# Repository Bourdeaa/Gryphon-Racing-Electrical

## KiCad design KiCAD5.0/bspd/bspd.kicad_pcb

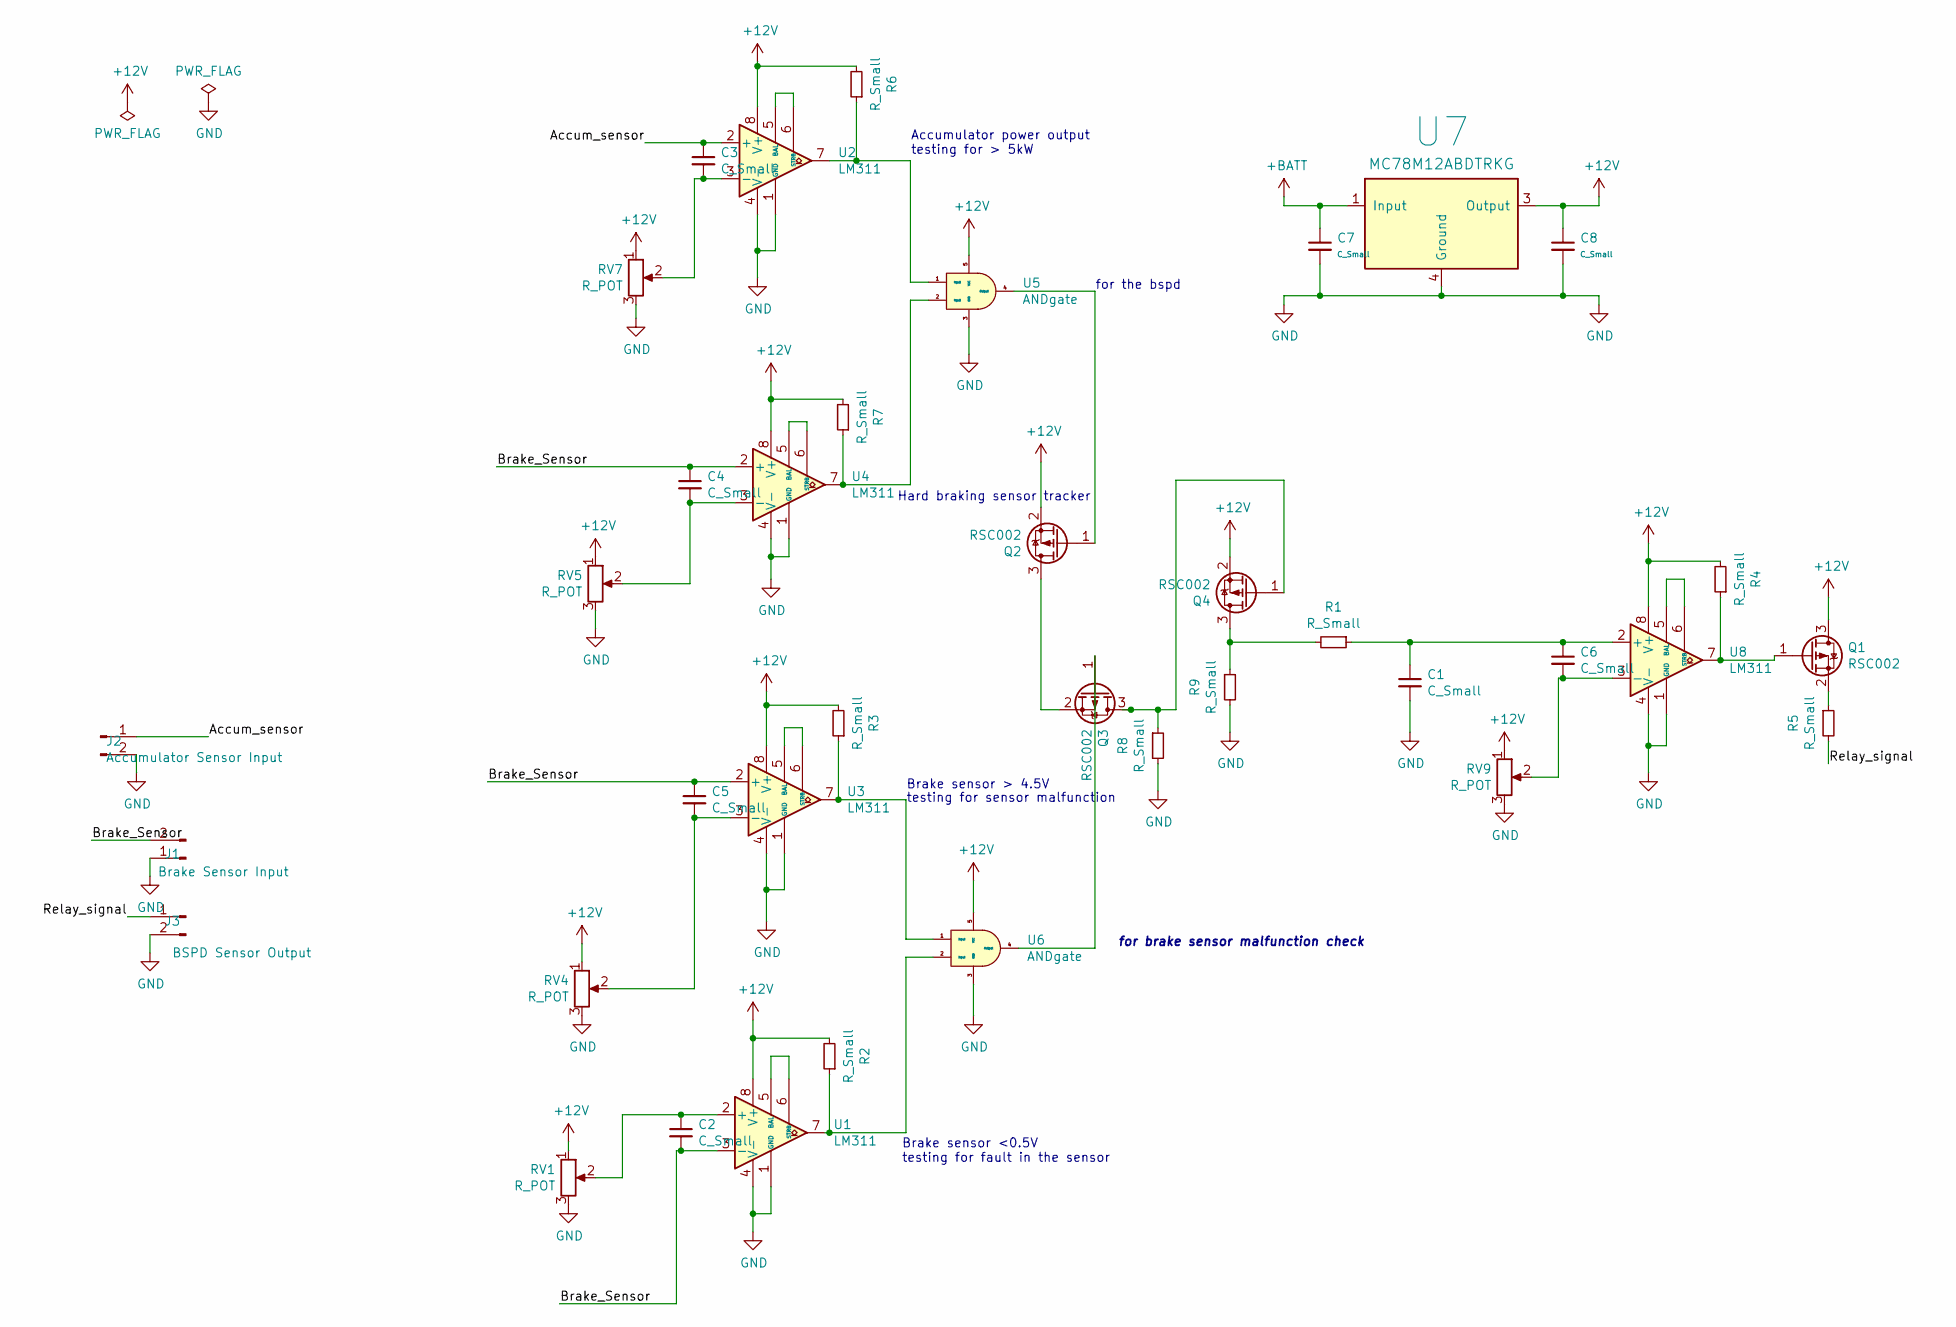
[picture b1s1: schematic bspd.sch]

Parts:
C1, C2, C3, C4, C5, C6, C7, C8: C_Small; C_1210_3225Metric_Pad1.33x2.70mm_HandSolder
J1: Brake Sensor Input; CUI_TBL001-500-02GY-2GY
J2: Accumulator Sensor Input; CUI_TBL001-500-02GY-2GY
J3: BSPD Sensor Output; CUI_TBL001-500-02GY-2GY
Q1, Q2, Q3, Q4: RSC002; BZT03C12-TR
R1, R2, R3, R4, R5, R6, R7, R8, R9: R_Small; R_0603_1608Metric_Pad0.98x0.95mm_HandSolder
RV1, RV4, RV5, RV7, RV9: R_POT; PT01-D120K2-B103
U1, U2, U3, U4, U8: LM311; LM311PW
U5, U6: ANDgate; SOT95P280X145-5N
U7: MC78M12ABDTRKG; TO229P990X238-4N

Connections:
+12V: C8.1, Q1.3 (D), Q2.2 (S), Q4.2 (S), R2.2, R3.2, R4.2, R6.2, R7.2, RV1.1, RV4.1, RV5.1, RV7.1, RV9.1, U1.8 (V+), U2.8 (V+), U3.8 (V+), U4.8 (V+), U5.5 (VCC), U6.5 (VCC), U7.3 (Output), U8.8 (V+)
+BATT: C7.1, U7.1 (Input)
/Accum_sensor: C3.1, J2.1, U2.2 (+)
/Brake_Sensor: C2.2, C4.1, C5.1, J1.2, U1.3 (-), U3.2 (+), U4.2 (+)
/Relay_signal: J3.1, R5.2
GND: C1.2, C7.2, C8.2, J1.1, J2.2, J3.2, R8.2, R9.2, RV1.3, RV4.3, RV5.3, RV7.3, RV9.3, U1.1 (GND), U1.4 (V-), U2.1 (GND), U2.4 (V-), U3.1 (GND), U3.4 (V-), U4.1 (GND), U4.4 (V-), U5.3 (GND), U6.3 (GND), U7.4 (Ground), U8.1 (GND), U8.4 (V-)
unnamed: C1.1, C6.1, R1.1, U8.2 (+)
unnamed: C2.1, RV1.2, U1.2 (+)
unnamed: C3.2, RV7.2, U2.3 (-)
unnamed: C4.2, RV5.2, U4.3 (-)
unnamed: C5.2, RV4.2, U3.3 (-)
unnamed: C6.2, RV9.2, U8.3 (-)
unnamed: Q1.1 (G), R4.1, U8.7
unnamed: Q1.2 (S), R5.1
unnamed: Q2.1 (G), U5.4 (Output)
unnamed: Q2.3 (D), Q3.2 (S)
unnamed: Q3.1 (G), U6.4 (Output)
unnamed: Q3.3 (D), Q4.1 (G), R8.1
unnamed: Q4.3 (D), R1.2, R9.1
unnamed: R2.1, U1.7, U6.2 (Input)
unnamed: R3.1, U3.7, U6.1 (Input)
unnamed: R6.1, U2.7, U5.1 (Input)
unnamed: R7.1, U4.7, U5.2 (Input)
unnamed: U1.5 (BAL), U1.6 (STRB)
unnamed: U2.5 (BAL), U2.6 (STRB)
unnamed: U3.5 (BAL), U3.6 (STRB)
unnamed: U4.5 (BAL), U4.6 (STRB)
unnamed: U8.5 (BAL), U8.6 (STRB)

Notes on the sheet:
for the bspd
for brake sensor malfunction check
Brake sensor <0.5V testing for fault in the sensor
Brake sensor > 4.5V
testing for sensor malfunction
Hard braking sensor tracker
Accumulator power output testing for > 5kW

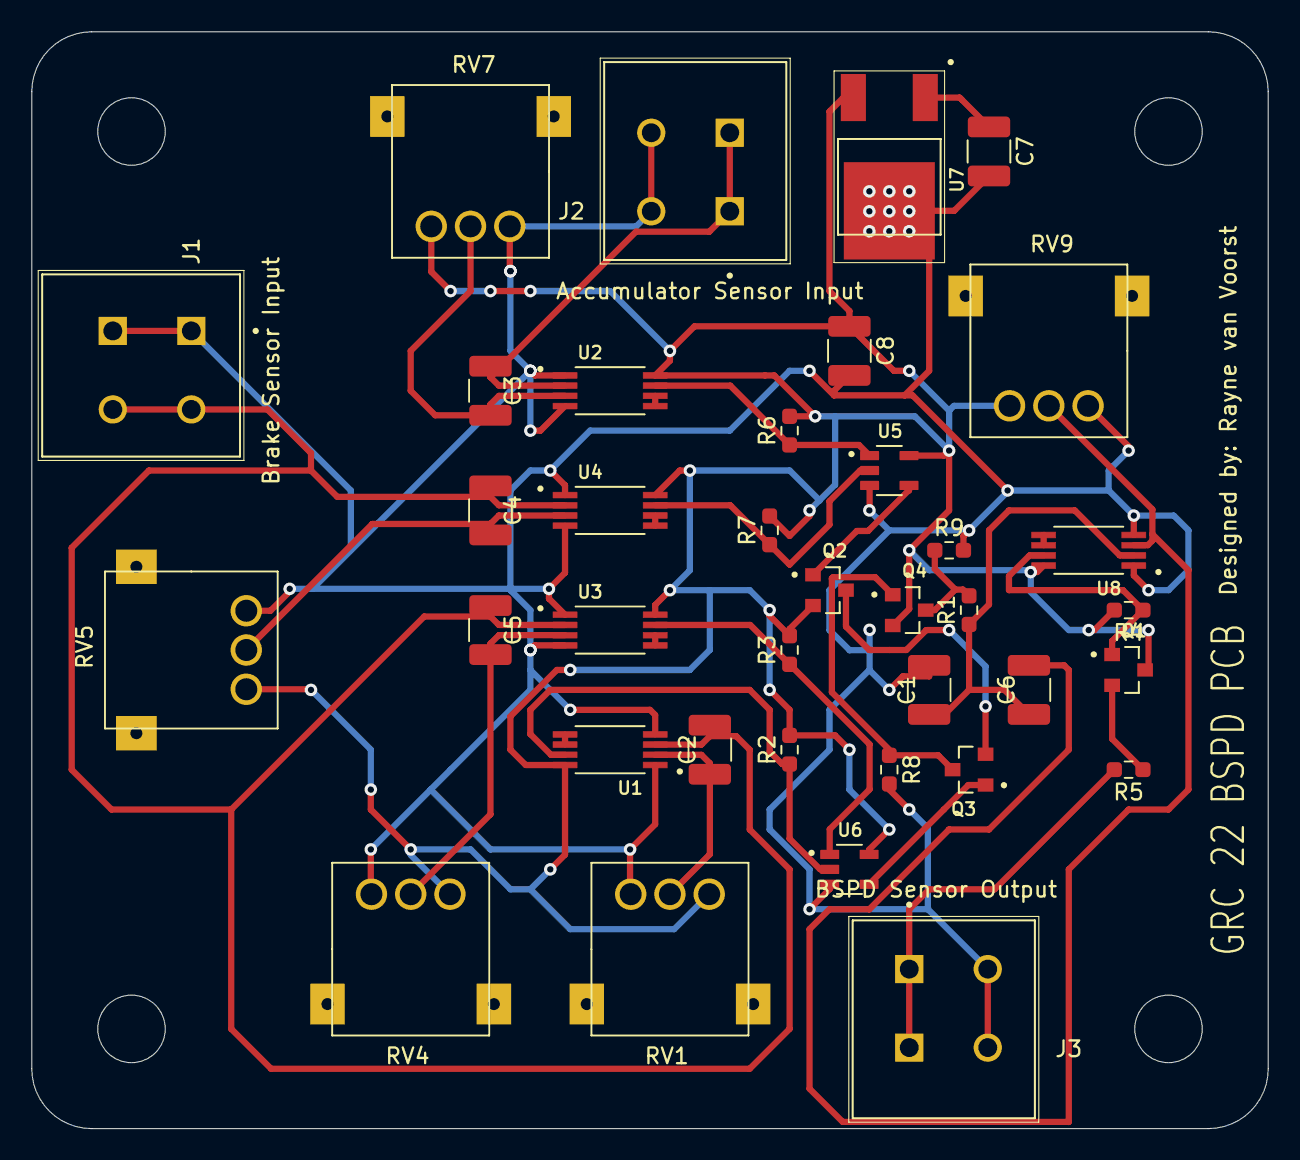
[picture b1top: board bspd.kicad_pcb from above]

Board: 2 copper layers, 78.7 x 69.9 mm, 37 parts (0 on the bottom side), 28 nets.

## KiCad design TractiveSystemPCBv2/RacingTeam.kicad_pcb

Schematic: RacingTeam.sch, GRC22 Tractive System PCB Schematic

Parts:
C1, C2: 470nF; C_0603_1608Metric_Pad1.08x0.95mm_HandSolder
C3, C4: 22μF; CAPE830X690N
C5, C6: 10nF; C_0603_1608Metric_Pad1.08x0.95mm_HandSolder
C7, C8: 100nF; C_0603_1608Metric_Pad1.08x0.95mm_HandSolder
C9, C10, C11, C12: 1μF; C_0603_1608Metric_Pad1.08x0.95mm_HandSolder
D1, D2: 12V; SOD57-10
D3, D8: LED; D_0805_2012Metric_Castellated
D4, D5, D6: Flyback; D_0805_2012Metric_Castellated
D7: D; D_0805_2012Metric_Castellated
F1, F2: Fuse_Small; FUSE_0154004.DRTL
J1: BusIn; TE_8PCV-02-006
J2: PowerInput; CUI_TBL001-500-02GY-2GY
J3: BrakePositionSensor; CUI_TBL001-500-02GY-2GY
J4: StartButton; CUI_TBL001-500-02GY-2GY
J5: Molex; 878310819
J6, J8, J10: BypassPin; PinHeader_1x01_P2.54mm_Vertical
J7: TSW-101-23-S-S; PinHeader_1x01_P2.54mm_Vertical
J9: PC Out; CUI_TBL001-500-02GY-2GY
J11: AIR Out; CUI_TBL001-500-02GY-2GY
J12: DischargeRelay; CUI_TBL001-500-02GY-2GY
JP1, JP2: Jumper; PinHeader_1x02_P2.54mm_Vertical
PS1: SPBW06F-12; CONV_SPBW06F-12; PARTREV N/A
Q1, Q2, Q3, Q7: 2N7002; 2N7002H6327XTSA2
Q4, Q5, Q6, Q8, Q9: RSC002; BZT03C12-TR
Q10: FMMT494QTA; SOT91P240X110-3N
Q11: RSC; BZT03C12-TR
R1, R2: 200kΩ; R_0805_2012Metric_Pad1.20x1.40mm_HandSolder
R3, R8: 25kΩ; R_0805_2012Metric_Pad1.20x1.40mm_HandSolder
R4, R5: 500kΩ; R_0805_2012Metric_Pad1.20x1.40mm_HandSolder
R6, R7: 150kΩ; R_0805_2012Metric_Pad1.20x1.40mm_HandSolder
R9, R10: 1kΩ; R_0603_1608Metric_Pad0.98x0.95mm_HandSolder
R11, R12: 0Ω; R_0603_1608Metric_Pad0.98x0.95mm_HandSolder
R14, R15, R16, R17: 100Ω; R_0603_1608Metric_Pad0.98x0.95mm_HandSolder
R18, R19: 20kΩ; R_0603_1608Metric_Pad0.98x0.95mm_HandSolder
R20, R21: 1.2kΩ; R_0603_1608Metric_Pad0.98x0.95mm_HandSolder
R22, R23, R28, R29: 10kΩ; R_0603_1608Metric_Pad0.98x0.95mm_HandSolder
R24, R26: 22kΩ; R_0603_1608Metric_Pad0.98x0.95mm_HandSolder
R25, R32: 499Ω; R_0603_1608Metric_Pad0.98x0.95mm_HandSolder
R27: 220kΩ; R_0603_1608Metric_Pad0.98x0.95mm_HandSolder
R30: 47kΩ; R_0603_1608Metric_Pad0.98x0.95mm_HandSolder
R31: 4.7kΩ; R_0603_1608Metric_Pad0.98x0.95mm_HandSolder
RV1, RV2: 10kΩ; PT01-D120K2-B103
U1, U2: LM2941LD; DFN400X400X80-9N
U3, U4: LM311; LM311PW
U5, U6: 4N35; OPTO_4N35SM
U7: NE555D; NE555PSRE4
U8: MC78M12ABDTRKG; TO229P990X238-4N

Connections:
+12V: C1.1, C2.1, PS1.6 (+VOUT), R18.2, R19.2, U1.3, U2.3, U3.8 (V+), U4.8 (V+), U5.1, U6.1
+BATT: C10.1, J2.2, PS1.2 (+VIN), U8.1 (Input)
/555Discharge: R26.2, R27.1, U7.7 (DIS)
/555DriveRED: Q7.3 (D), Q9.1 (G), R29.2
/555Output: Q7.1 (G), U7.3 (Q)
/555Reset: Q1.3 (D), Q4.1 (G), R24.2, U7.4 (R)
/555Trigger: C9.1, R27.2, U7.2 (TR), U7.6 (THR)
/AIR+: D6.1 (K), J11.1, Q2.1 (G), Q6.3 (D)
/BusLine: J1.1, R2.1
/BusOutPrecharge: F2.1, R3.1, R8.2, R12.2
/BusOutTSAL: F1.2, R6.2, R7.1, R11.2
/BusRefTSAL: D1.1 (K), F1.1, J8.1, R11.1, R14.2
/BusReturn: J1.2, R3.2
/Common: J3.2, J4.1
/Discharge: D5.1 (K), J12.1, Q2.2 (S), Q5.3 (D)
/Green+: J5.2, JP1.2, Q4.3 (D)
/InvertBus: Q1.1 (G), R23.1, U6.4
/OBLEDGreen: D3.2 (A), JP1.1
/OBLEDRed: D8.2 (A), JP2.2
/OBLEDResistorGreen: D3.1 (K), R25.1
/OBLEDResistorRed: D8.1 (K), R32.1
/PreChargeV+: C5.1, R17.1, U3.2 (+)
/Precharge-: D4.2 (A), J9.2, Q3.3 (D), Q5.1 (G)
/PrechargeCompOUT: R19.1, R20.1, U3.7
/PrechargeOPTO: Q3.1 (G), Q6.1 (G), Q11.1 (G), R22.2, U5.4
/PrechargeRef: C4.1, J7.1, R16.2, RV2.1, U2.5
/PrechargeV-: C5.2, R16.1, U3.3 (-)
/RED+: J5.3, JP2.1, Q9.3 (D)
/RTDLatch: J3.1, Q8.1 (G), Q10.2 (C), R28.1
/RTDOutput: C12.1, Q8.3 (D), Q11.2 (S)
/RTDReady: J5.4, Q11.3 (D)
/TSALCompOut: R18.1, R21.1, U4.7
/TSALRef: C3.1, J6.1, R15.2, RV1.1, U1.5
/TSAL_LM311V+: C6.1, R14.1, U4.2 (+)
/TSAL_LM311V-: C6.2, R15.1, U4.3 (-)
GLV+: C7.1, C11.1, D4.1 (K), J5.1, J9.1, Q2.3 (D), Q4.2 (S), Q5.2 (S), Q6.2 (S), Q8.2 (S), Q9.2 (S), R24.1, R26.1, R28.2, R29.1, U5.5, U6.5, U7.8 (VCC), U8.3 (Output)
GLV-: C7.2, C8.2, C9.2, C10.2, C11.2, D5.2 (A), D6.2 (A), D7.2 (A), J2.1, J4.2, J5.5, J5.6, J5.7, J5.8, J11.2, J12.2, PS1.1 (-VIN), Q1.2 (S), Q3.2 (S), Q7.2 (S), Q10.3 (E), R22.1, R23.2, R25.2, R30.2, R32.2, U7.1 (GND), U8.4 (Ground)
GND: C1.2, C2.2, C3.2, C4.2, D1.2 (A), D2.2 (A), PS1.7 (-VOUT), R9.1, R10.1, U1.1, U1.2, U1.7, U1.9, U2.1, U2.2, U2.7, U2.9, U3.1 (GND), U3.4 (V-), U4.1 (GND), U4.4 (V-)
unnamed: C8.1, U7.5 (CV)
unnamed: C12.2, D7.1 (K), R31.2
unnamed: D2.1 (K), F2.2, J10.1, R12.1, R17.2
unnamed: Q10.1 (B), R30.1, R31.1
unnamed: R1.1, R2.2
unnamed: R1.2, R4.2
unnamed: R4.1, R5.2
unnamed: R5.1, R6.1
unnamed: R7.2, R8.1
unnamed: R9.2, RV1.2, U1.8
unnamed: R10.2, RV2.2, U2.8
unnamed: R20.2, U5.2
unnamed: R21.2, U6.2
unnamed: U3.5 (BAL), U3.6 (STRB)
unnamed: U4.5 (BAL), U4.6 (STRB)

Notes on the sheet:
TSAL
Isolation Barrier
TSAL Trigger Voltage = 60V Voltage Division Ratio = 0.8857 60V- 60(0.8857) = 6.86V
Comparator Logic If V- > V+ || Output is pulled to GND If V+ > V- || Inner Transistor is not conducting
12V+ - High Voltage Regulated 12V (From HV Regulator) GND - High Voltage Regulated Isolated Ground (From HV Regulator) +BATT - Unregulated Battery Supply + -BATT - Unregulated Battery Supply - (Synced to GLV-) GLV+ - Grounded Low Voltage + (from GLV Regulator) GLV- - Grounded Low Voltage - (From GL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
If=10mA
GLV
BoardOutputs
Discharge Control
Power Symbol Definitions
GLV Regulator
Source Gate Drain
Ready To Drive
PCR
AIR
BoardInputs
PreCharge Control
RelayOutputs
Latch Activation
Precharge Trigger Voltage = 525V Voltage Division Ratio = 0.9857 525V- 525(0.9857) = 7.5V
Trim Pot to 5.9k
Trim Pot to 5.4k

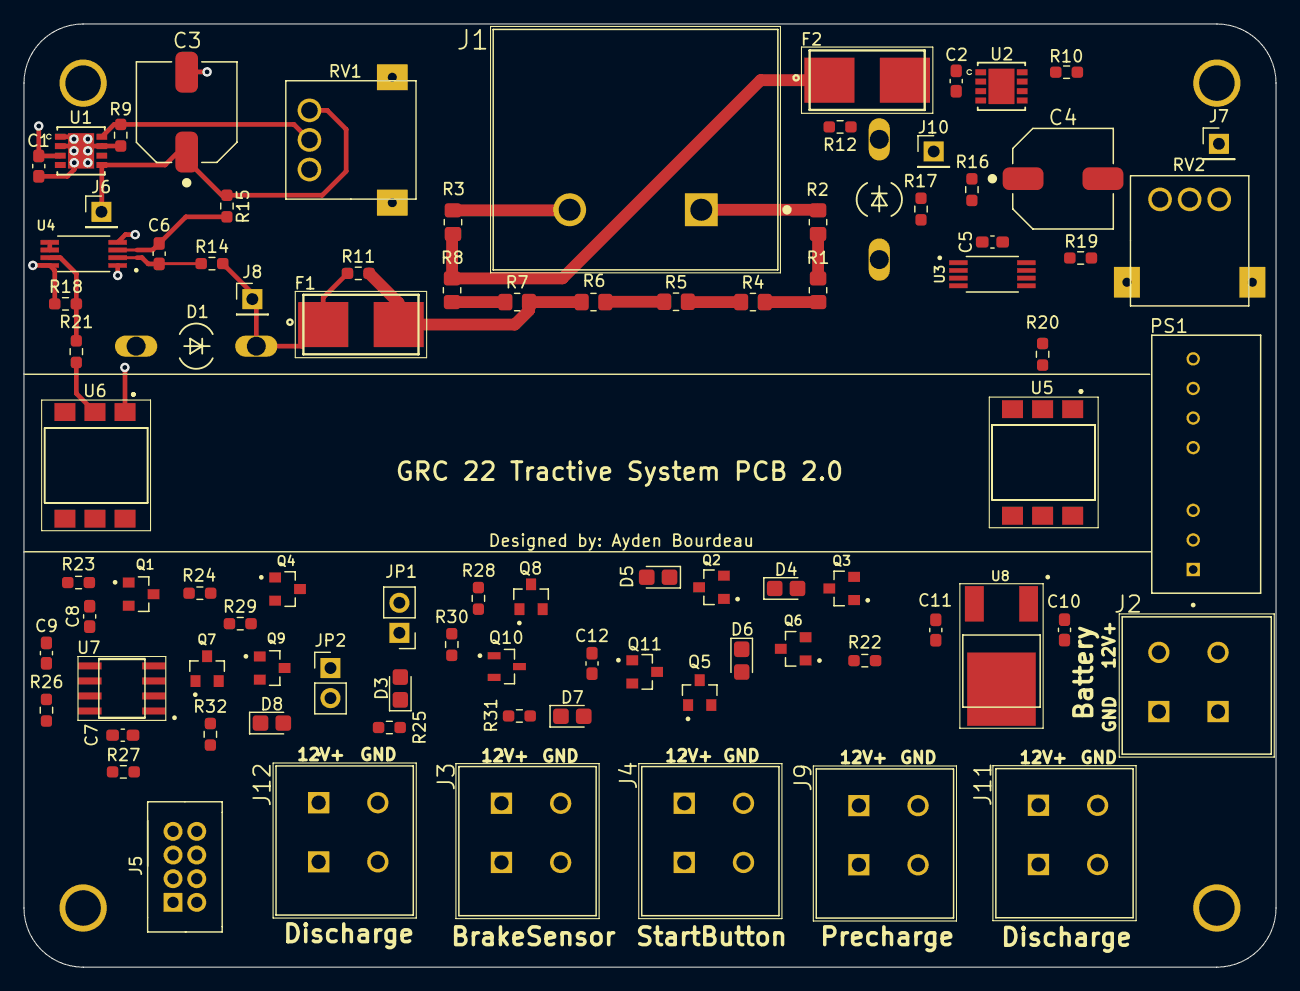
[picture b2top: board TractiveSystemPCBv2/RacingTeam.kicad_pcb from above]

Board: 4 copper layers, 105.8 x 79.7 mm, 89 parts (0 on the bottom side), 53 nets.

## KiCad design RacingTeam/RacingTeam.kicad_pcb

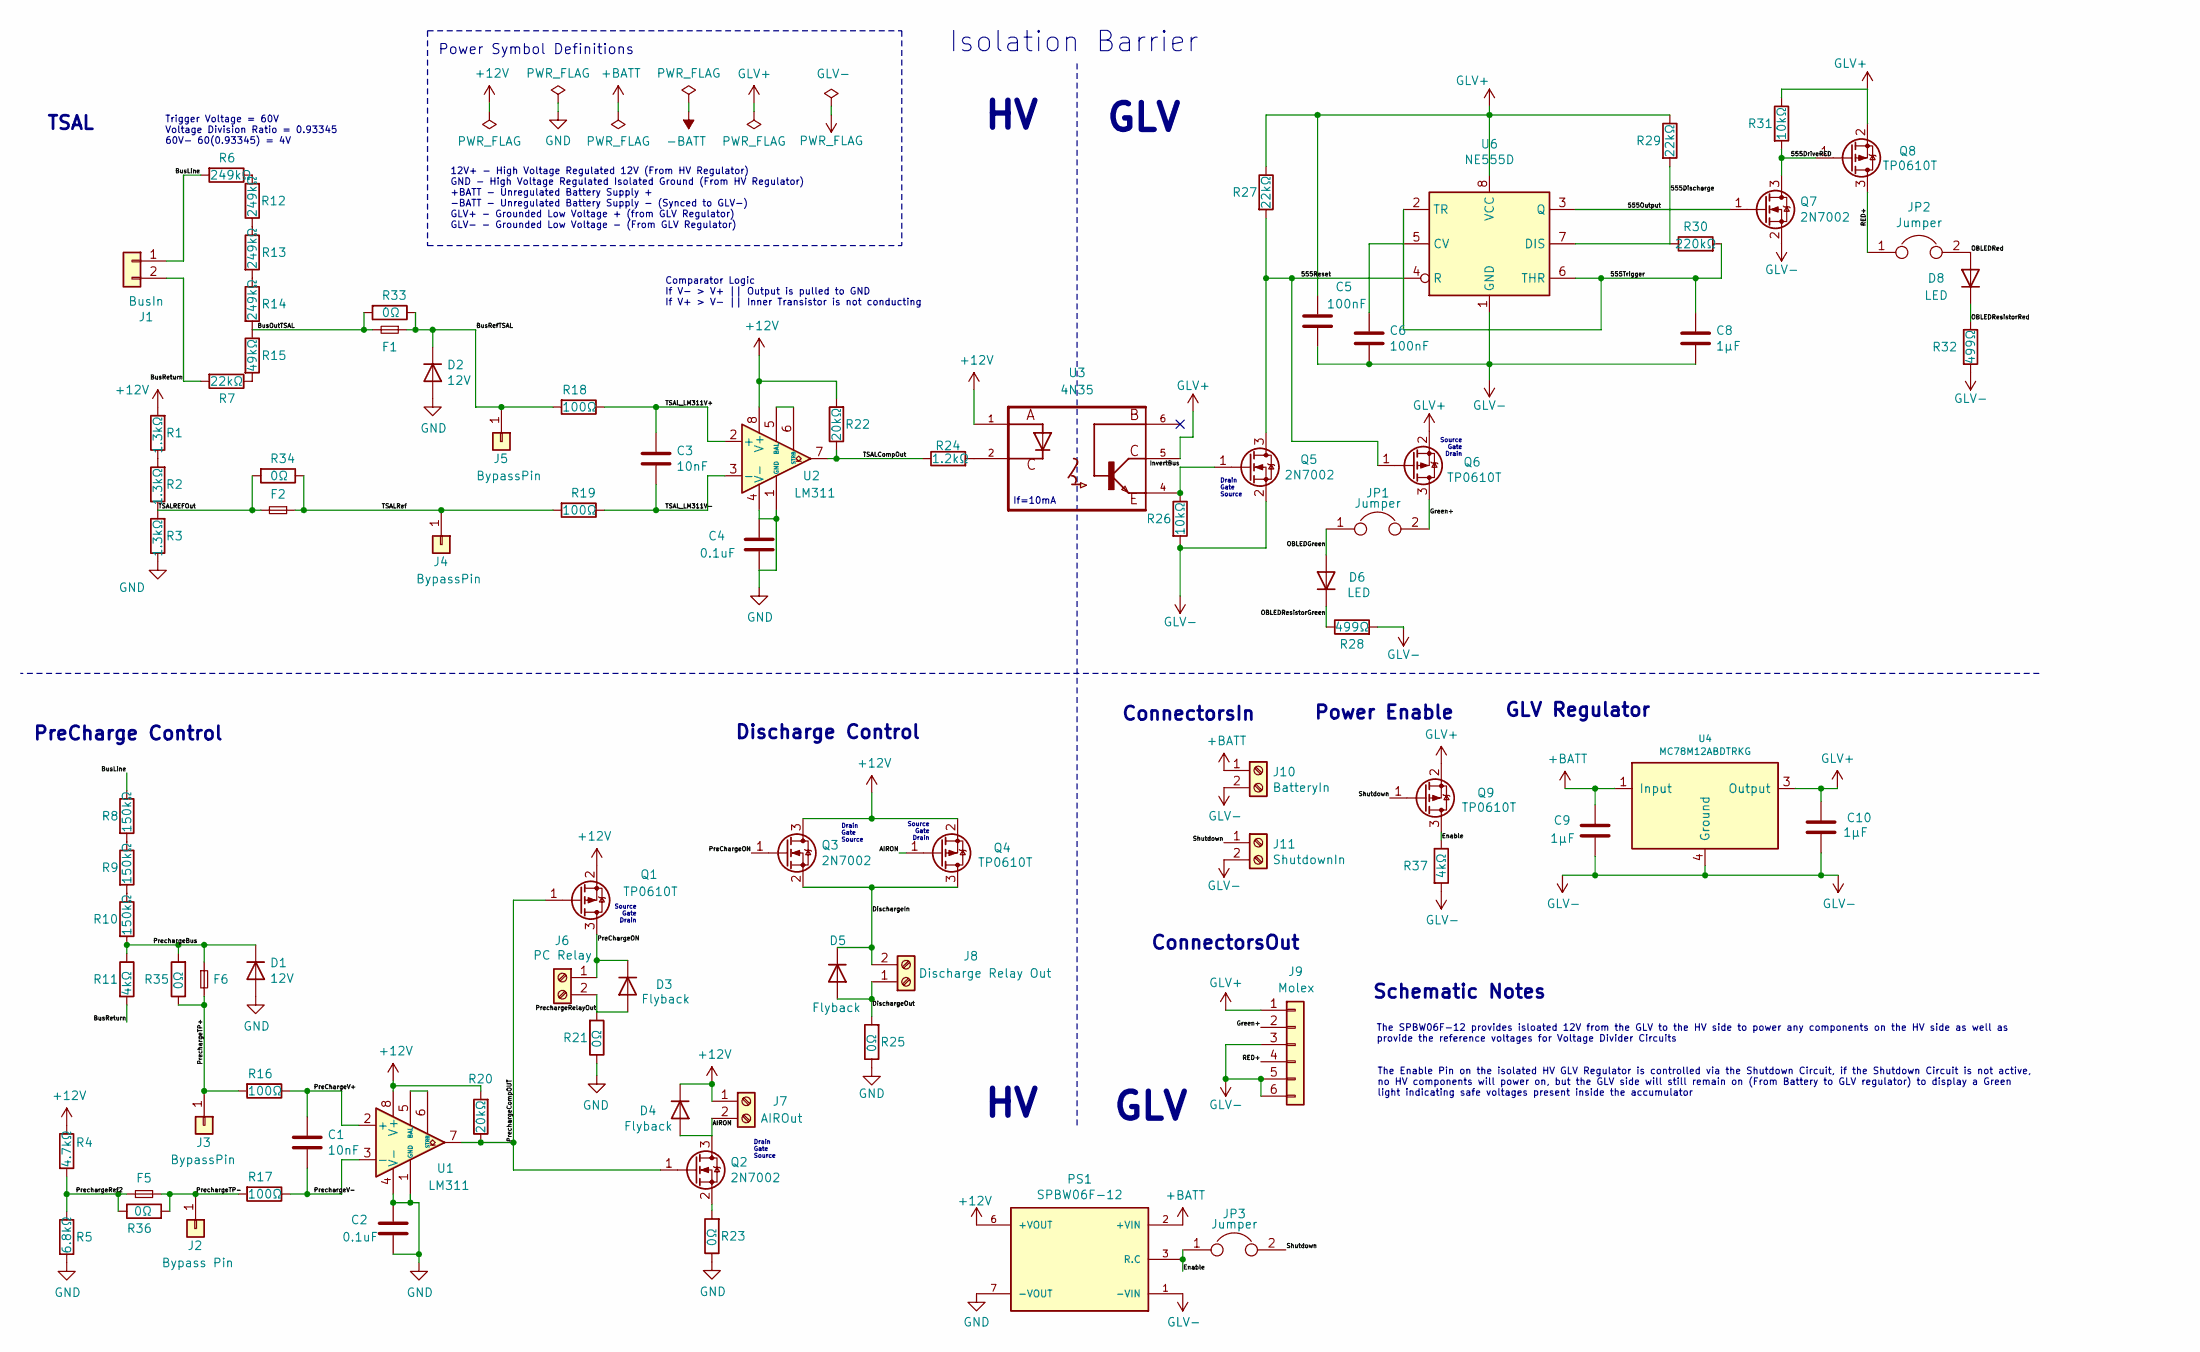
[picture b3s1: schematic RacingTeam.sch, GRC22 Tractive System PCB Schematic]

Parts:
C1, C3: 10nF; C_0603_1608Metric_Pad1.08x0.95mm_HandSolder
C2, C4: 0.1uF; C_0603_1608Metric_Pad1.08x0.95mm_HandSolder
C5, C6: 100nF; C_0603_1608Metric_Pad1.08x0.95mm_HandSolder
C8, C9, C10: 1μF; C_0603_1608Metric_Pad1.08x0.95mm_HandSolder
D1, D2: 12V; SOD57-10
D3, D4, D5: Flyback; D_0805_2012Metric_Castellated
D6, D8: LED; D_0603_1608Metric_Castellated
F1, F2, F5, F6: Fuse_Small; FUSE_0154004.DRTL
J1: BusIn; TE_8PCV-02-006
J2: Bypass Pin; PinHeader_1x01_P2.54mm_Vertical
J3, J4, J5: BypassPin; PinHeader_1x01_P2.54mm_Vertical
J6: PC Relay; CUI_TBL001-500-02GY-2GY
J7: AIROut; CUI_TBL001-500-02GY-2GY
J8: Discharge Relay Out; CUI_TBL001-500-02GY-2GY
J9: Molex
J10: BatteryIn; CUI_TBL001-500-02GY-2GY
J11: ShutdownIn; CUI_TBL001-500-02GY-2GY
JP1, JP2, JP3: Jumper; PinHeader_1x02_P2.54mm_Vertical
PS1: SPBW06F-12; CONV_SPBW06F-12; PARTREV N/A
Q1, Q4, Q6, Q8, Q9: TP0610T; 2N7002H6327XTSA2_v2
Q2, Q3, Q5, Q7: 2N7002; 2N7002H6327XTSA2
R1, R2, R3: 1.3kΩ; R_0603_1608Metric_Pad0.98x0.95mm_HandSolder
R4: 4.7kΩ; R_0603_1608Metric_Pad0.98x0.95mm_HandSolder
R5: 6.8kΩ; R_0603_1608Metric_Pad0.98x0.95mm_HandSolder
R6, R12, R13, R14: 249kΩ; R_0805_2012Metric_Pad1.20x1.40mm_HandSolder
R7: 22kΩ; R_0805_2012Metric_Pad1.20x1.40mm_HandSolder
R8, R9, R10: 150kΩ; R_0805_2012Metric_Pad1.20x1.40mm_HandSolder
R11: 4kΩ; R_0805_2012Metric_Pad1.20x1.40mm_HandSolder
R15: 49kΩ; R_0805_2012Metric_Pad1.20x1.40mm_HandSolder
R16, R17, R18, R19: 100Ω; R_0603_1608Metric_Pad0.98x0.95mm_HandSolder
R20, R22: 20kΩ; R_0603_1608Metric_Pad0.98x0.95mm_HandSolder
R21, R23, R25, R33, R34, R35, R36: 0Ω; R_0805_2012Metric_Pad1.20x1.40mm_HandSolder
R24: 1.2kΩ; R_0603_1608Metric_Pad0.98x0.95mm_HandSolder
R26, R31: 10kΩ; R_0603_1608Metric_Pad0.98x0.95mm_HandSolder
R27, R29: 22kΩ; R_0603_1608Metric_Pad0.98x0.95mm_HandSolder
R28, R32: 499Ω; R_0603_1608Metric_Pad0.98x0.95mm_HandSolder
R30: 220kΩ; R_0603_1608Metric_Pad0.98x0.95mm_HandSolder
R37: 4kΩ; R_0603_1608Metric_Pad0.98x0.95mm_HandSolder
U1, U2: LM311; LM311PW
U3: 4N35; OPTO_4N35SM
U4: MC78M12ABDTRKG; TO229P990X238-4N
U6: NE555D; NE555PSRE4

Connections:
+12V: D4.1 (K), J7.1, PS1.6 (+VOUT), Q1.2 (S), Q3.3 (D), Q4.2 (S), R1.2, R4.1, R20.2, R22.2, U1.8 (V+), U2.8 (V+), U3.1
+BATT: C9.1, J10.1, PS1.2 (+VIN), U4.1 (Input)
/555Discharge: R29.2, R30.1, U6.7 (DIS)
/555DriveRED: Q7.3 (D), Q8.1 (G), R31.2
/555Output: Q7.1 (G), U6.3 (Q)
/555Reset: Q5.3 (D), Q6.1 (G), R27.2, U6.4 (R)
/555Trigger: C8.1, R30.2, U6.2 (TR), U6.6 (THR)
/AIRON: D4.2 (A), J7.2, Q2.3 (D), Q4.1 (G)
/BusLine: J1.1, R6.2, R8.1
/BusOutTSAL: F1.2, R14.2, R15.1, R33.2
/BusRefTSAL: D2.1 (K), F1.1, J5.1, R18.2, R33.1
/BusReturn: J1.2, R7.2, R11.2
/DischargeIn: D5.1 (K), J8.2, Q3.2 (S), Q4.3 (D)
/DischargeOut: D5.2 (A), J8.1, R25.2
/Enable: JP3.1, PS1.3 (R.C), Q9.3 (D), R37.1
/Green+: J9.2, JP1.2, Q6.3 (D)
/InvertBus: Q5.1 (G), R26.1, U3.4
/OBLEDGreen: D6.2 (A), JP1.1
/OBLEDRed: D8.2 (A), JP2.2
/OBLEDResistorGreen: D6.1 (K), R28.1
/OBLEDResistorRed: D8.1 (K), R32.1
/PreChargeON: D3.1 (K), J6.1, Q1.3 (D), Q3.1 (G)
/PreChargeV+: C1.1, R16.1, U1.2 (+)
/PrechargeBus: D1.1 (K), F6.1, R10.2, R11.1, R35.2
/PrechargeCompOUT: Q1.1 (G), Q2.1 (G), R20.1, U1.7
/PrechargeRef2: F5.1, R4.2, R5.1, R36.1
/PrechargeRelayOut: D3.2 (A), J6.2, R21.2
/PrechargeTP+: F6.2, J3.1, R16.2, R35.1
/PrechargeTP-: F5.2, J2.1, R17.2, R36.2
/PrechargeV-: C1.2, R17.1, U1.3 (-)
/RED+: J9.4, JP2.1, Q8.3 (D)
/Shutdown: J11.1, JP3.2, Q9.1 (G)
/TSALCompOut: R22.1, R24.1, U2.7
/TSALREFOut: F2.2, R2.1, R3.2, R34.2
/TSALRef: F2.1, J4.1, R19.2, R34.1
/TSAL_LM311V+: C3.1, R18.1, U2.2 (+)
/TSAL_LM311V-: C3.2, R19.1, U2.3 (-)
GLV+: C5.1, C10.1, J9.1, Q6.2 (S), Q8.2 (S), Q9.2 (S), R27.1, R29.1, R31.1, U3.5, U4.3 (Output), U6.8 (VCC)
GLV-: C5.2, C6.2, C8.2, C9.2, C10.2, J9.3, J9.5, J9.6, J10.2, J11.2, PS1.1 (-VIN), Q5.2 (S), Q7.2 (S), R26.2, R28.2, R32.2, R37.2, U4.4 (Ground), U6.1 (GND)
GND: C2.1, C2.2, C4.1, C4.2, D1.2 (A), D2.2 (A), PS1.7 (-VOUT), R3.1, R5.2, R21.1, R23.1, R25.1, U1.1 (GND), U1.4 (V-), U2.1 (GND), U2.4 (V-)
unnamed: C6.1, U6.5 (CV)
unnamed: Q2.2 (S), R23.2
unnamed: R1.1, R2.2
unnamed: R8.2, R9.1
unnamed: R9.2, R10.1
unnamed: R12.1, R13.1
unnamed: R6.1, R12.2
unnamed: R13.2, R14.1
unnamed: R7.1, R15.2
unnamed: R24.2, U3.2
unnamed: U1.5 (BAL), U1.6 (STRB)
unnamed: U2.5 (BAL), U2.6 (STRB)

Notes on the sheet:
TSAL
Isolation Barrier
Trigger Voltage = 60V Voltage Division Ratio = 0.93345 60V- 60(0.93345) = 4V
Comparator Logic If V- > V+ || Output is pulled to GND If V+ > V- || Inner Transistor is not conducting
12V+ - High Voltage Regulated 12V (From HV Regulator) GND - High Voltage Regulated Isolated Ground (From HV Regulator) +BATT - Unregulated Battery Supply + -BATT - Unregulated Battery Supply - (Synced to GLV-) GLV+ - Grounded Low Voltage + (from GLV Regulator) GLV- - Grounded Low Voltage - (From GL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
If=10mA
ConnectorsIn
GLV
ConnectorsOut
Source Gate Drain
Drain Gate Source
PreCharge Control
Discharge Control
Power Symbol Definitions
The SPBW06F-12 provides isloated 12V from the GLV to the HV side to power any components on the HV side as well as provide the reference voltages for Voltage Divider Circuits
The Enable Pin on the isolated HV GLV Regulator is controlled via the Shutdown Circuit, if the Shutdown Circuit is not active, no HV components will power on, but the GLV side will still remain on (From Battery to GLV regulator) to display a Green light indicating safe voltages present inside the a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
Schematic Notes
GLV Regulator
Power Enable

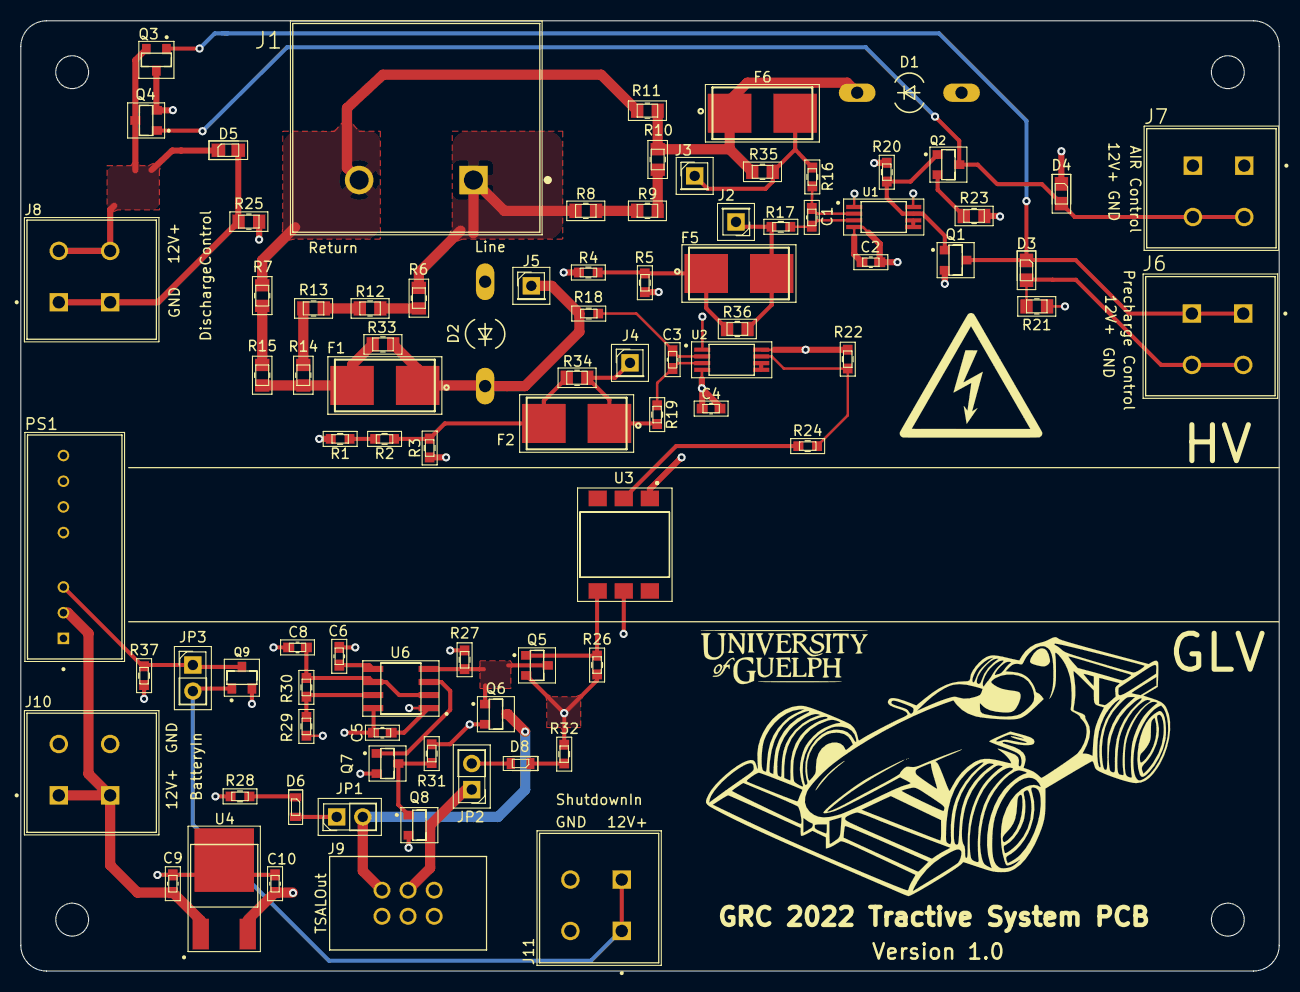
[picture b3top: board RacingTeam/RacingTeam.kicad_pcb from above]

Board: 4 copper layers, 122.5 x 92.5 mm, 86 parts (0 on the bottom side), 52 nets.

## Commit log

2022-03-22 Update ESF.zip, ESFSymbols.dcm, and 9 more files...
2022-03-22 Update SPAN02A12.kicad_mod, EC3SAW.STEP, and 8 more files...
2022-03-23 Update RacingTeam.zip, PCBBom.xlsx, and 2 more files...
2022-03-24 Update 2N7002H6327XTSA2.kicad_mod, 4N35SM.kicad_mod, and 21 more files...
2022-03-27 Update FUSE_0154004.DRTL.kicad_mod, GRC2022.mod, and 15 more files...
2022-03-28 Update FSAELogo.kicad_mod, GRC2022.mod, and 11 more files...
2022-03-28 Update RacingTeam.kicad_pcb and RacingTeam.kicad_pcb-bak
2022-03-28 Update RacingTeam.kicad_pcb, RacingTeam.kicad_pcb-bak, and 3 more files...
2022-03-30 Update RacingTeamPCB.dcm, RacingTeamPCB.lib, and 6 more files...
2022-04-01 Update PCBBom.xlsx, RacingTeam.kicad_pcb, and 4 more files...
2022-04-04 Update 2N7002H6327XTSA2.kicad_mod, 4N35SM.kicad_mod, and 69 more files...
2022-04-05 Update GRC22Footprints.mod, C_0603_1608Metric.step, and 19 more files...
2022-04-07 Update GRC22Footprints.mod, CONV_SPBW06F-12.kicad_mod, and 43 more files...
2022-04-11 Update Precharge-cache.lib, Precharge.pro, and 326 more files...
2022-04-12 Update GRC22Symbols.dcm, GRC22Symbols.lib, and 3 more files...
2022-04-18 Update ESFSymbols.dcm, ESFSymbols.lib, and 3 more files...
2022-06-15 Update RacingTeam.kicad_pcb-bak, RacingTeam.xml, and 38 more files...
2022-06-18 Update GRC Logo.jpg, GRCLogo.kicad_mod, and 21 more files...
2022-09-25 Update GRC22Footprints.mod, 2N7002H6327XTSA2.kicad_mod, and 496 more files...
2022-10-07 Update CODEOWNERS, RacingTeam.pro, and RacingTeam.sch-bak
2022-10-11 Update TractiveSystemPCB_v3-2022-09-24_203121.zip, TractiveSystemPCB_v3-2022-09-25_180032.zip, and 7 more files...
2022-10-12 Update KiCADReferencingInstructions.docx, TractiveSystemPCB_v3-2022-09-27_114516.zip, and 9 more files...
2022-10-12 Update Comparator.kicad_sym, Connector.kicad_sym, and 11 more files...
2022-10-16 Update C_0603_1608Metric.step, LM311PW.STEP, and 37 more files...
2022-10-19 Update BSPD 2.0-2022-10-19_141737.zip, BSPD 2.0.kicad_pcb, and 22 more files...
2022-10-31 Added accumulator schematic
2022-10-31 Added GLV connection to precharge symbol
2022-11-04 Update ShutdownBoard.kicad_pcb, ShutdownBoard.kicad_pro, and 3 more files...
2022-11-05 Update BSPD 2.0-2022-11-05_114535.zip, Connector_Generic.kicad_sym, and 16 more files...
2022-11-05 Update Connector_Generic.kicad_sym, glv+.kicad_sym, and 15 more files...
